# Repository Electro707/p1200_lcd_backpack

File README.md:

# P1200 - LCB Backpack
# WIP

*Image of board on an LCD during development*

This project is for a generic LCD backpack, similar to the many ones out there, with some distinct features that lead me to build my own:

- Negative voltage for the LCD Bias
    - This was the biggest reason I made this project, as I had an older LCD that wouldn't work unless the LCD is biased to -2v. This is OK as most LCDs can be biased to -9v below VCC, I think?
- Both 5v and 3.3v power and data compatibility
- UART, SPI, and I2C protocols
- The ability to offload some functionality to this backpack, such as animations on the LCD

# Project Structure:

- E1201: The KiCAD PCB files
- F1202: The firmware folder
- Release: All locked in files

# PCB Jumper and Notes

TODO: this section

# PCB Errata
The ERRATA's for the latest revision PCB can be found in [`ERRATA.md`](ERRATA.md)

# Firmware
The [firmware for this project](F1202/) is targeted towards the MCU on board (PIC16F18155).

To use the project, open it up in MPLAB IDE (v6.35 used), with PIC-AS 4.00 (comes with XC8) and device pack `PIC16F1xxxx_DFP==1.31.465` (other version should be OK, noted for repeatability).

The project is written in assembly.
Why? Why not?
This was mostly for my learning of writing an entire firmware in bare assembly and getting familiar with the PIC architecture. I found it fun.

More info on the firmware, including the communication protocol, can be found in [F1202/README.md](F1202/README.md)

# License
This project is licensed under [GPLv3](LICENSE.md)**

** This excludes the files in `E1201/SparkFun-Qwiic.pretty`, as they [came from the Sparkfun](https://www.sparkfun.com/qwiic)

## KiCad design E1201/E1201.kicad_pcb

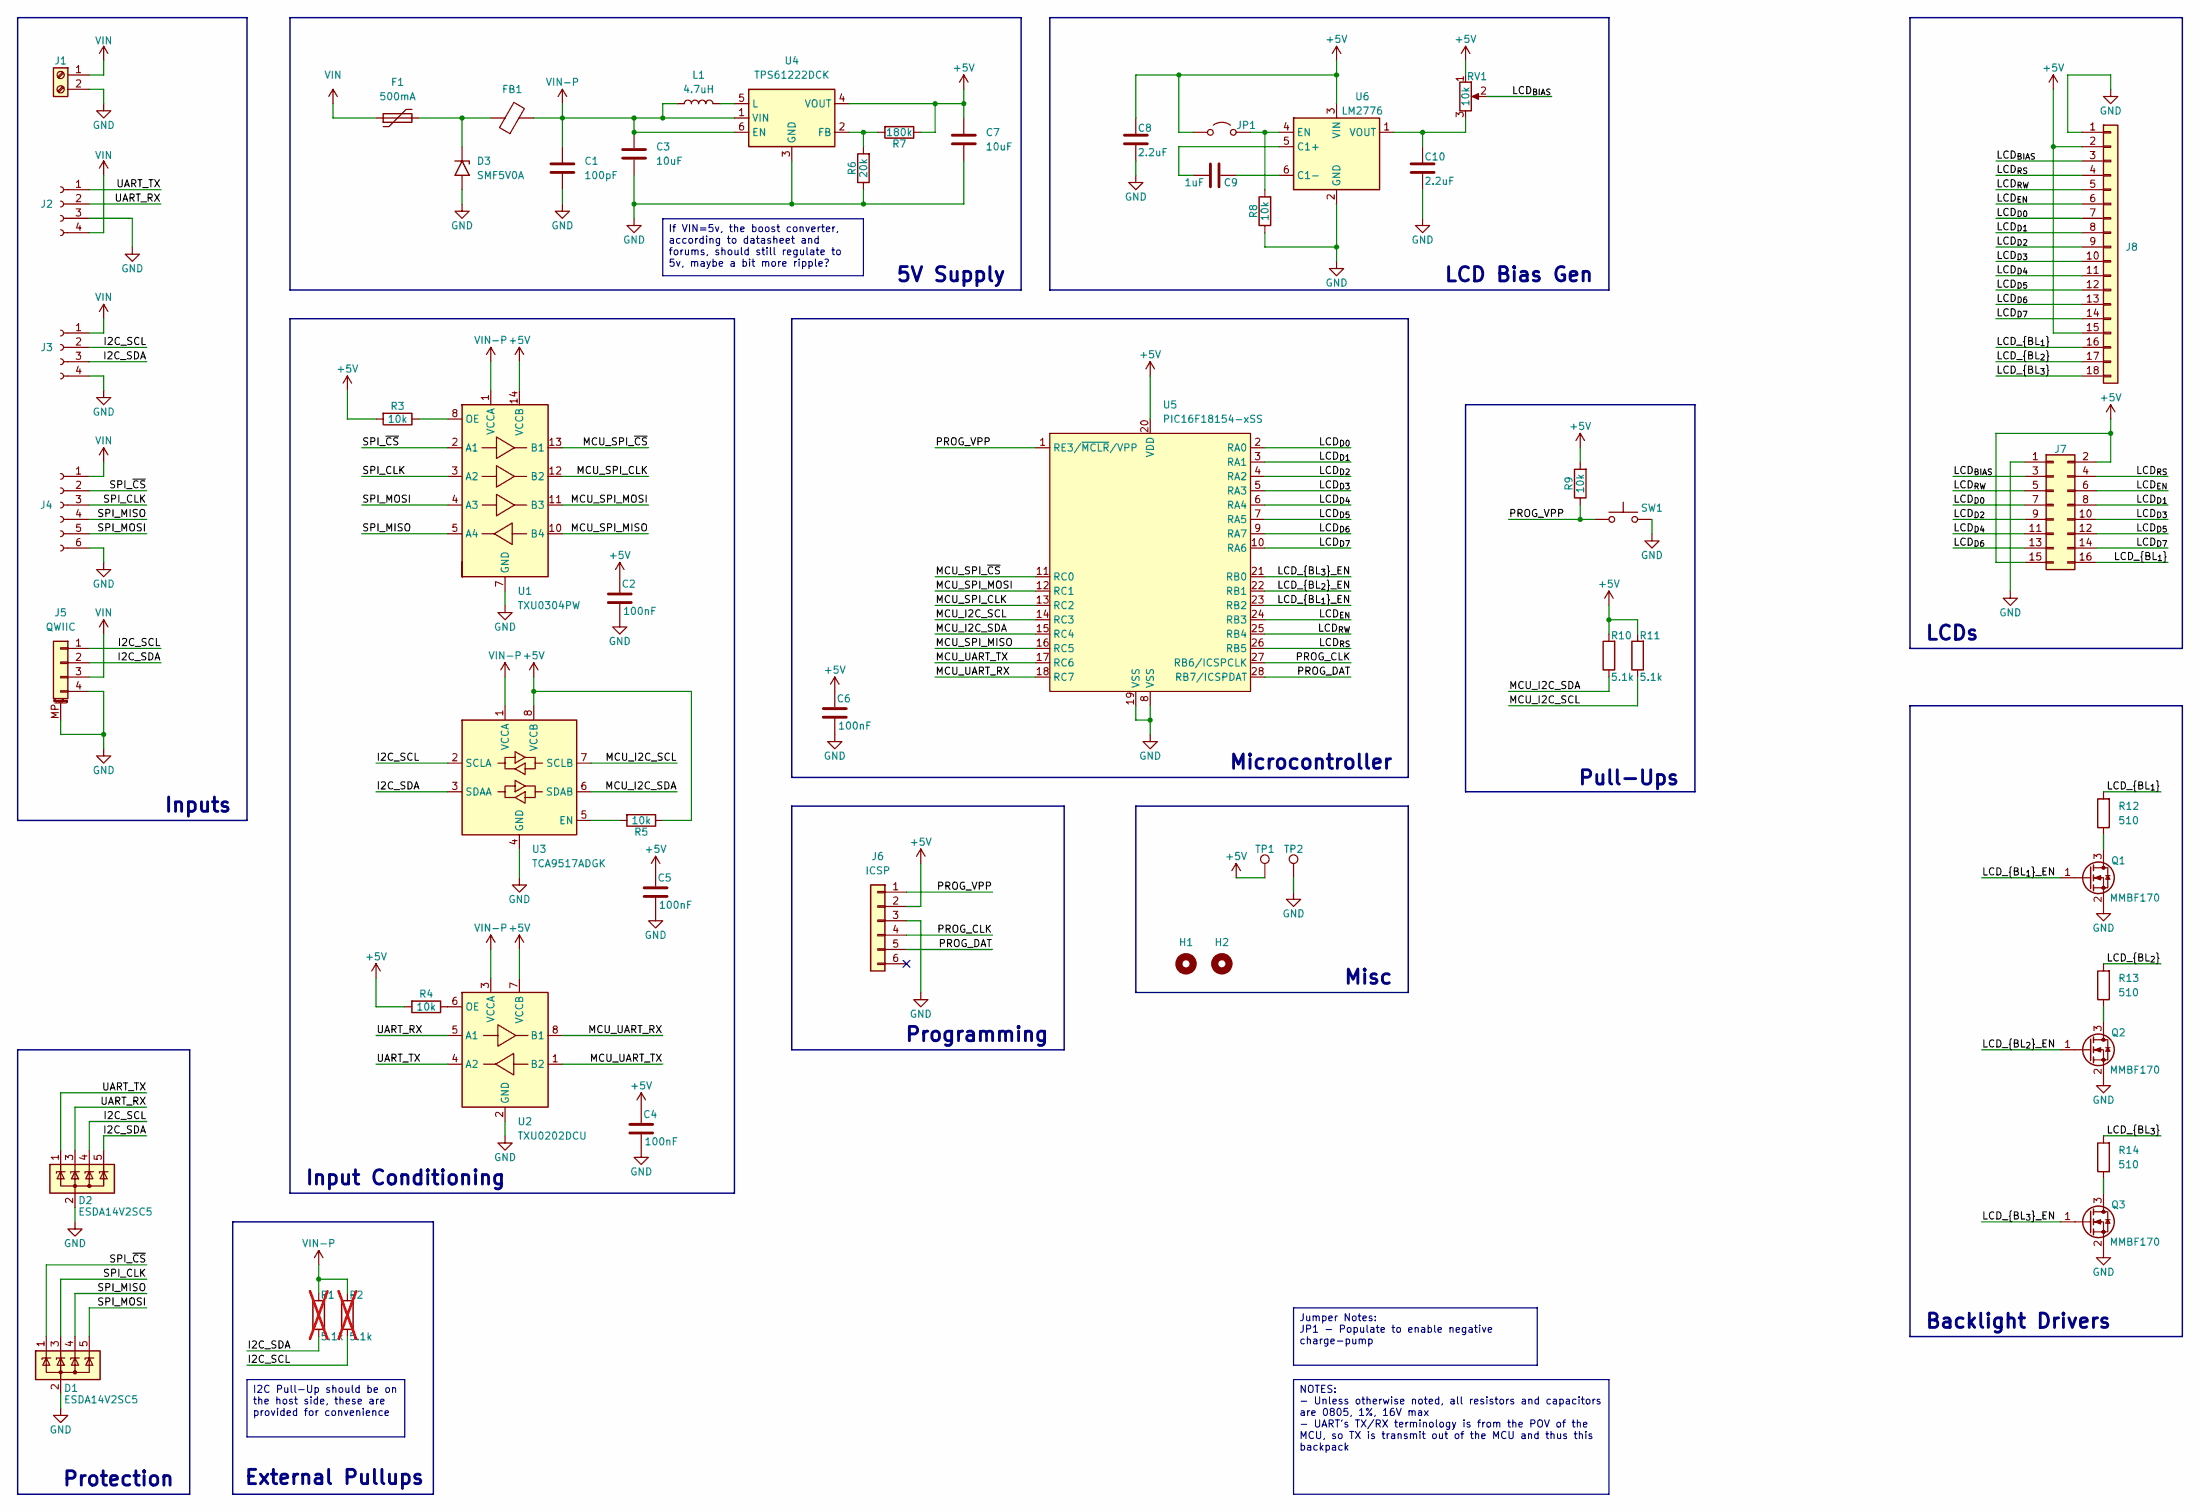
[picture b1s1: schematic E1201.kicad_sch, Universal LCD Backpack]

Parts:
C1: 100pF; C_0805_2012Metric_Pad1.18x1.45mm_HandSolder
C2, C4, C5, C6: 100nF; C_0805_2012Metric_Pad1.18x1.45mm_HandSolder
C3, C7: 10uF; C_0805_2012Metric_Pad1.18x1.45mm_HandSolder
C8, C10: 2.2uF; C_0805_2012Metric_Pad1.18x1.45mm_HandSolder
C9: 1uF; C_0805_2012Metric_Pad1.18x1.45mm_HandSolder
D1, D2: ESDA14V2SC5; SOT-23-5
D3: SMF5V0A; D_SMF
F1: 500mA; Fuse_1206_3216Metric_Pad1.42x1.75mm_HandSolder
FB1: FerriteBead; L_0805_2012Metric_Pad1.05x1.20mm_HandSolder
H1, H2: MountingHole; MountingHole_3.2mm_M3
J1: Screw_Terminal_01x02; PinSocket_1x02_P2.54mm_Vertical
J2, J3: Conn_01x04_Socket; PinSocket_1x04_P2.54mm_Vertical
J4: Conn_01x06_Socket; PinSocket_1x06_P2.54mm_Vertical
J5: QWIIC; JST_SH_SM04B-SRSS-TB_1x04-1MP_P1.00mm_Horizontal
J6: ICSP; Tag-Connect_TC2030-IDC-NL_2x03_P1.27mm_Vertical
J7: Conn_02x08_Odd_Even; PinHeader_2x08_P2.54mm_Vertical
J8: Conn_01x18; PinSocket_1x18_P2.54mm_Vertical
JP1: Jumper_2_Open; SolderJumper-2_P1.3mm_Open_TrianglePad1.0x1.5mm
L1: 4.7uH; L_1210_3225Metric; Part Number CBC3225T4R7MR
Q1, Q2, Q3: MMBF170; SOT-23
R1, R2: 5.1k; R_0805_2012Metric_Pad1.20x1.40mm_HandSolder; not fitted
R3, R4, R5, R8, R9: 10k; R_0805_2012Metric_Pad1.20x1.40mm_HandSolder
R6: 20k; R_0805_2012Metric_Pad1.20x1.40mm_HandSolder
R7: 180k; R_0805_2012Metric_Pad1.20x1.40mm_HandSolder
R10, R11: 5.1k; R_0805_2012Metric_Pad1.20x1.40mm_HandSolder
R12, R13, R14: 510; R_0805_2012Metric_Pad1.20x1.40mm_HandSolder
RV1: 10k; Potentiometer_Bourns_3214X_Vertical
SW1: SW_Push; SW_Push_1P1T_NO_CK_KMR2
TP1, TP2: TestPoint; TestPoint_Pad_1.5x1.5mm
U1: TXU0304PW; TSSOP-14_4.4x5mm_P0.65mm
U2: TXU0202DCU; VSSOP-8_2.3x2mm_P0.5mm
U3: TCA9517ADGK; VSSOP-8_3x3mm_P0.65mm
U4: TPS61222DCK; Texas_R-PDSO-G6
U5: PIC16F18154-xSS; SSOP-28_5.3x10.2mm_P0.65mm
U6: LM2776; SOT-23-6

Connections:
+5V: C2.2, C4.2, C5.2, C6.2, C7.2, C8.2, J6.2, J7.2, J7.15, J8.2, J8.15, JP1.1 (A), R3.2, R4.2, R5.1, R7.1, R9.2, R10.2, R11.2, RV1.1, TP1.1 (1_1), U1.14 (VCCB), U2.7 (VCCB), U3.8 (VCCB), U4.4 (VOUT), U5.20 (VDD), U6.3 (VIN)
/I2C_SCL: D2.4 (K), J3.2, J5.1, R2.1, U3.2 (SCLA)
/I2C_SDA: D2.5 (K), J3.3, J5.2, R1.1, U3.3 (SDAA)
/LCD_{BIAS}: J7.3, J8.3, RV1.2
/LCD_{BL_{1}}: J7.16, J8.16, R12.2
/LCD_{BL_{1}}_EN: Q1.1 (G), U5.23 (RB2)
/LCD_{BL_{2}}: J8.17, R13.2
/LCD_{BL_{2}}_EN: Q2.1 (G), U5.22 (RB1)
/LCD_{BL_{3}}: J8.18, R14.2
/LCD_{BL_{3}}_EN: Q3.1 (G), U5.21 (RB0)
/LCD_{D0}: J7.7, J8.7, U5.2 (RA0)
/LCD_{D1}: J7.8, J8.8, U5.3 (RA1)
/LCD_{D2}: J7.9, J8.9, U5.4 (RA2)
/LCD_{D3}: J7.10, J8.10, U5.5 (RA3)
/LCD_{D4}: J7.11, J8.11, U5.6 (RA4)
/LCD_{D5}: J7.12, J8.12, U5.7 (RA5)
/LCD_{D6}: J7.13, J8.13, U5.9 (RA7)
/LCD_{D7}: J7.14, J8.14, U5.10 (RA6)
/LCD_{EN}: J7.6, J8.6, U5.24 (RB3)
/LCD_{RS}: J7.4, J8.4, U5.26 (RB5)
/LCD_{RW}: J7.5, J8.5, U5.25 (RB4)
/MCU_I2C_SCL: R11.1, U3.7 (SCLB), U5.14 (RC3)
/MCU_I2C_SDA: R10.1, U3.6 (SDAB), U5.15 (RC4)
/MCU_SPI_CLK: U1.12 (B2), U5.13 (RC2)
/MCU_SPI_MISO: U1.10 (B4), U5.16 (RC5)
/MCU_SPI_MOSI: U1.11 (B3), U5.12 (RC1)
/MCU_SPI_~CS: U1.13 (B1), U5.11 (RC0)
/MCU_UART_RX: U2.8 (B1), U5.18 (RC7)
/MCU_UART_TX: U2.1 (B2), U5.17 (RC6)
/PROG_CLK: J6.4, U5.27 (RB6/ICSPCLK)
/PROG_DAT: J6.5, U5.28 (RB7/ICSPDAT)
/PROG_VPP: J6.1, R9.1, SW1.2, U5.1 (RE3/~MCLR/VPP)
/SPI_CLK: D1.3 (K), J4.3, U1.3 (A2)
/SPI_MISO: D1.4 (K), J4.4, U1.5 (A4)
/SPI_MOSI: D1.5 (K), J4.5, U1.4 (A3)
/SPI_~CS: D1.1 (K), J4.2, U1.2 (A1)
/UART_RX: D2.3 (K), J2.2, U2.5 (A1)
/UART_TX: D2.1 (K), J2.1, U2.4 (A2)
GND: C1.1, C2.1, C3.1, C4.1, C5.1, C6.1, C7.1, C8.1, C10.1, D1.2 (A), D2.2 (A), D3.2 (A2), J1.2, J2.3, J3.4, J4.6, J5.4, J5.MP (MountPin), J6.3, J7.1, J8.1, Q1.2 (S), Q2.2 (S), Q3.2 (S), R6.1, R8.1, SW1.1, TP2.1 (1_1), U1.7 (GND), U2.2 (GND), U3.4 (GND), U4.3 (GND), U5.8 (VSS), U5.19 (VSS), U6.2 (GND)
unnamed: D3.1 (A1), F1.2, FB1.1
unnamed: JP1.2 (B), R8.2, U6.4 (EN)
unnamed: Q1.3 (D), R12.1
unnamed: Q2.3 (D), R13.1
unnamed: Q3.3 (D), R14.1
unnamed: R3.1, U1.8 (OE)
unnamed: R4.1, U2.6 (OE)
unnamed: R5.2, U3.5 (EN)
unnamed: R6.2, R7.2, U4.2 (FB)
unnamed: L1.2, U4.5 (L)
unnamed: C9.1, U6.5 (C1+)
unnamed: C9.2, U6.6 (C1-)
unnamed: C10.2, RV1.3, U6.1 (VOUT)
VIN: F1.1, J1.1, J2.4, J3.1, J4.1, J5.3
VIN-P: C1.2, C3.2, FB1.2, L1.1, R1.2, R2.2, U1.1 (VCCA), U2.3 (VCCA), U3.1 (VCCA), U4.1 (VIN), U4.6 (EN)

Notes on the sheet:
Input Conditioning
LCD Bias Gen
Pull-Ups
External Pullups
Misc
5V Supply
LCDs
Backlight Drivers
Inputs
Protection
Microcontroller
Programming
If VIN=5v, the boost converter, according to datasheet and forums, should still regulate to 5v, maybe a bit more ripple?
I2C Pull-Up should be on the host side, these are provided for convenience
Jumper Notes: JP1 - Populate to enable negative charge-pump
NOTES: - Unless otherwise noted, all resistors and capacitors are 0805, 1%, 16V max - UART's TX/RX terminology is from the POV of the MCU, so TX is transmit out of the MCU and thus this backpack

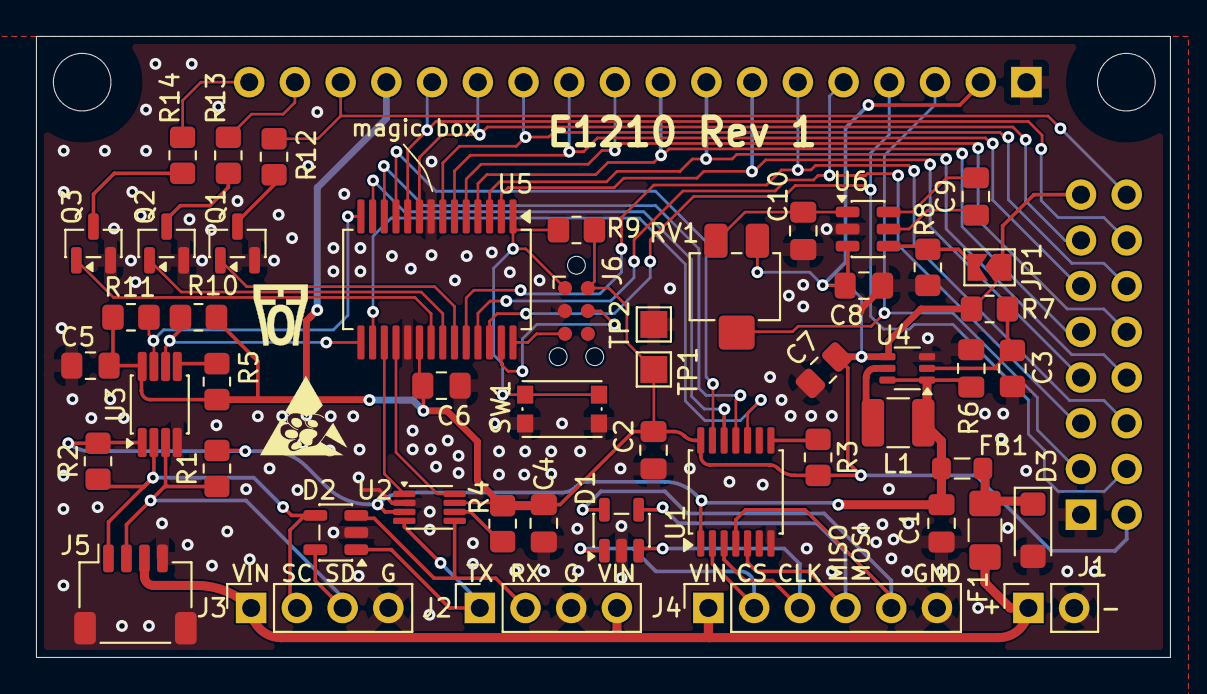
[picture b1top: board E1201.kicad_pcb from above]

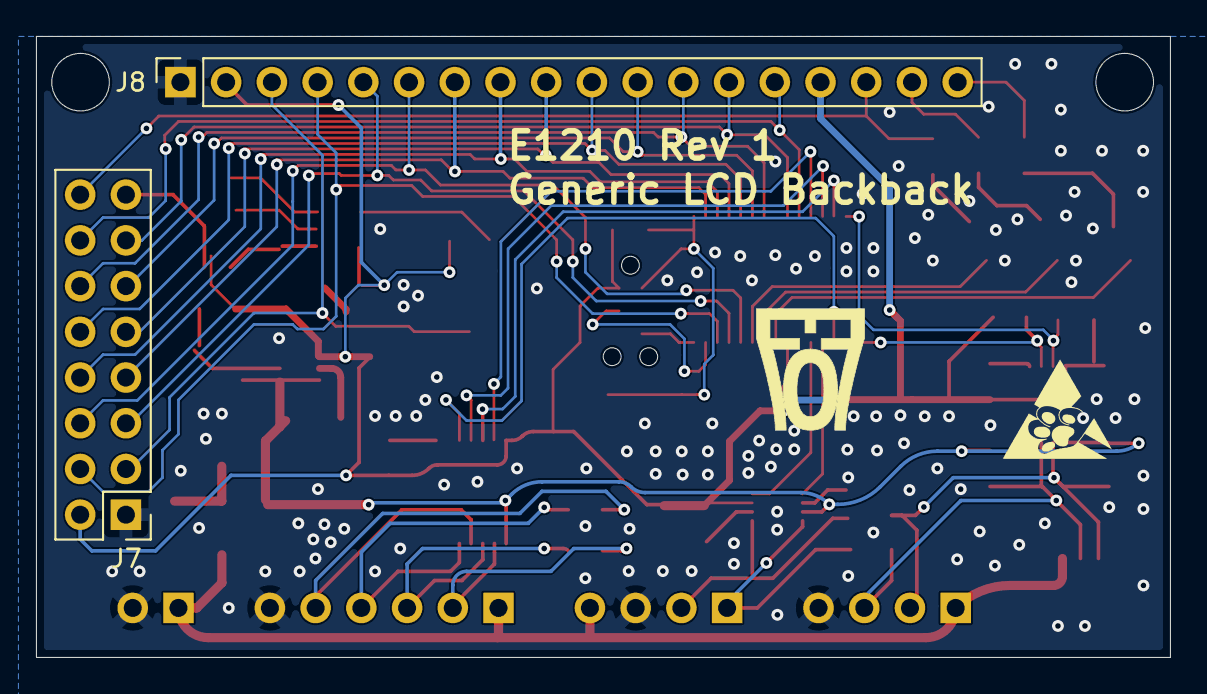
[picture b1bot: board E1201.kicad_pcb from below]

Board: 2 copper layers, 63.0 x 34.5 mm, 54 parts (2 on the bottom side), 54 nets.

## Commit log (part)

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2026-06-13 save point
